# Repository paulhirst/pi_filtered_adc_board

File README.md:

# pi_filtered_adc_board
PCB for R-pi with 8-channel ADC with 2nd order active low pass filters.

This is a KiCad schematic and PCB design for a PCB that connects to a
Raspberry Pi via the 40-pin GPIO connector. The board hosts an 8-channel
ADC connected vi SPI to the R-Pi, with single supply op-amps and passive
component positions to implement a 2nd-order Butterworth low-pass filter
on each channel. 

A convenient pin-grid is supplies to connect the ADC to the SPI0 or SPI1 
interfaces on the R-Pi, or to connect the SPI interface of the ADC to any
R-Pi GPIO pins.

If you don't want to implement 2nd order filters on the inputs, you can simply
omit the filter capacitors and replace resistors with wire links to use the 
opamps and simple buffers, or you could place resistors to set gain.

Resistor placements are provided to allow for example forming a potential 
divider with an on-board resistor and an off-board thermistor. The on-board
resistor placements can be shorted to provide +3.3 or +5v (selectable) on the
inputs D connector, providing for either 2 or 3-pin inputs (ie resistor or
potentiometer style inputs).

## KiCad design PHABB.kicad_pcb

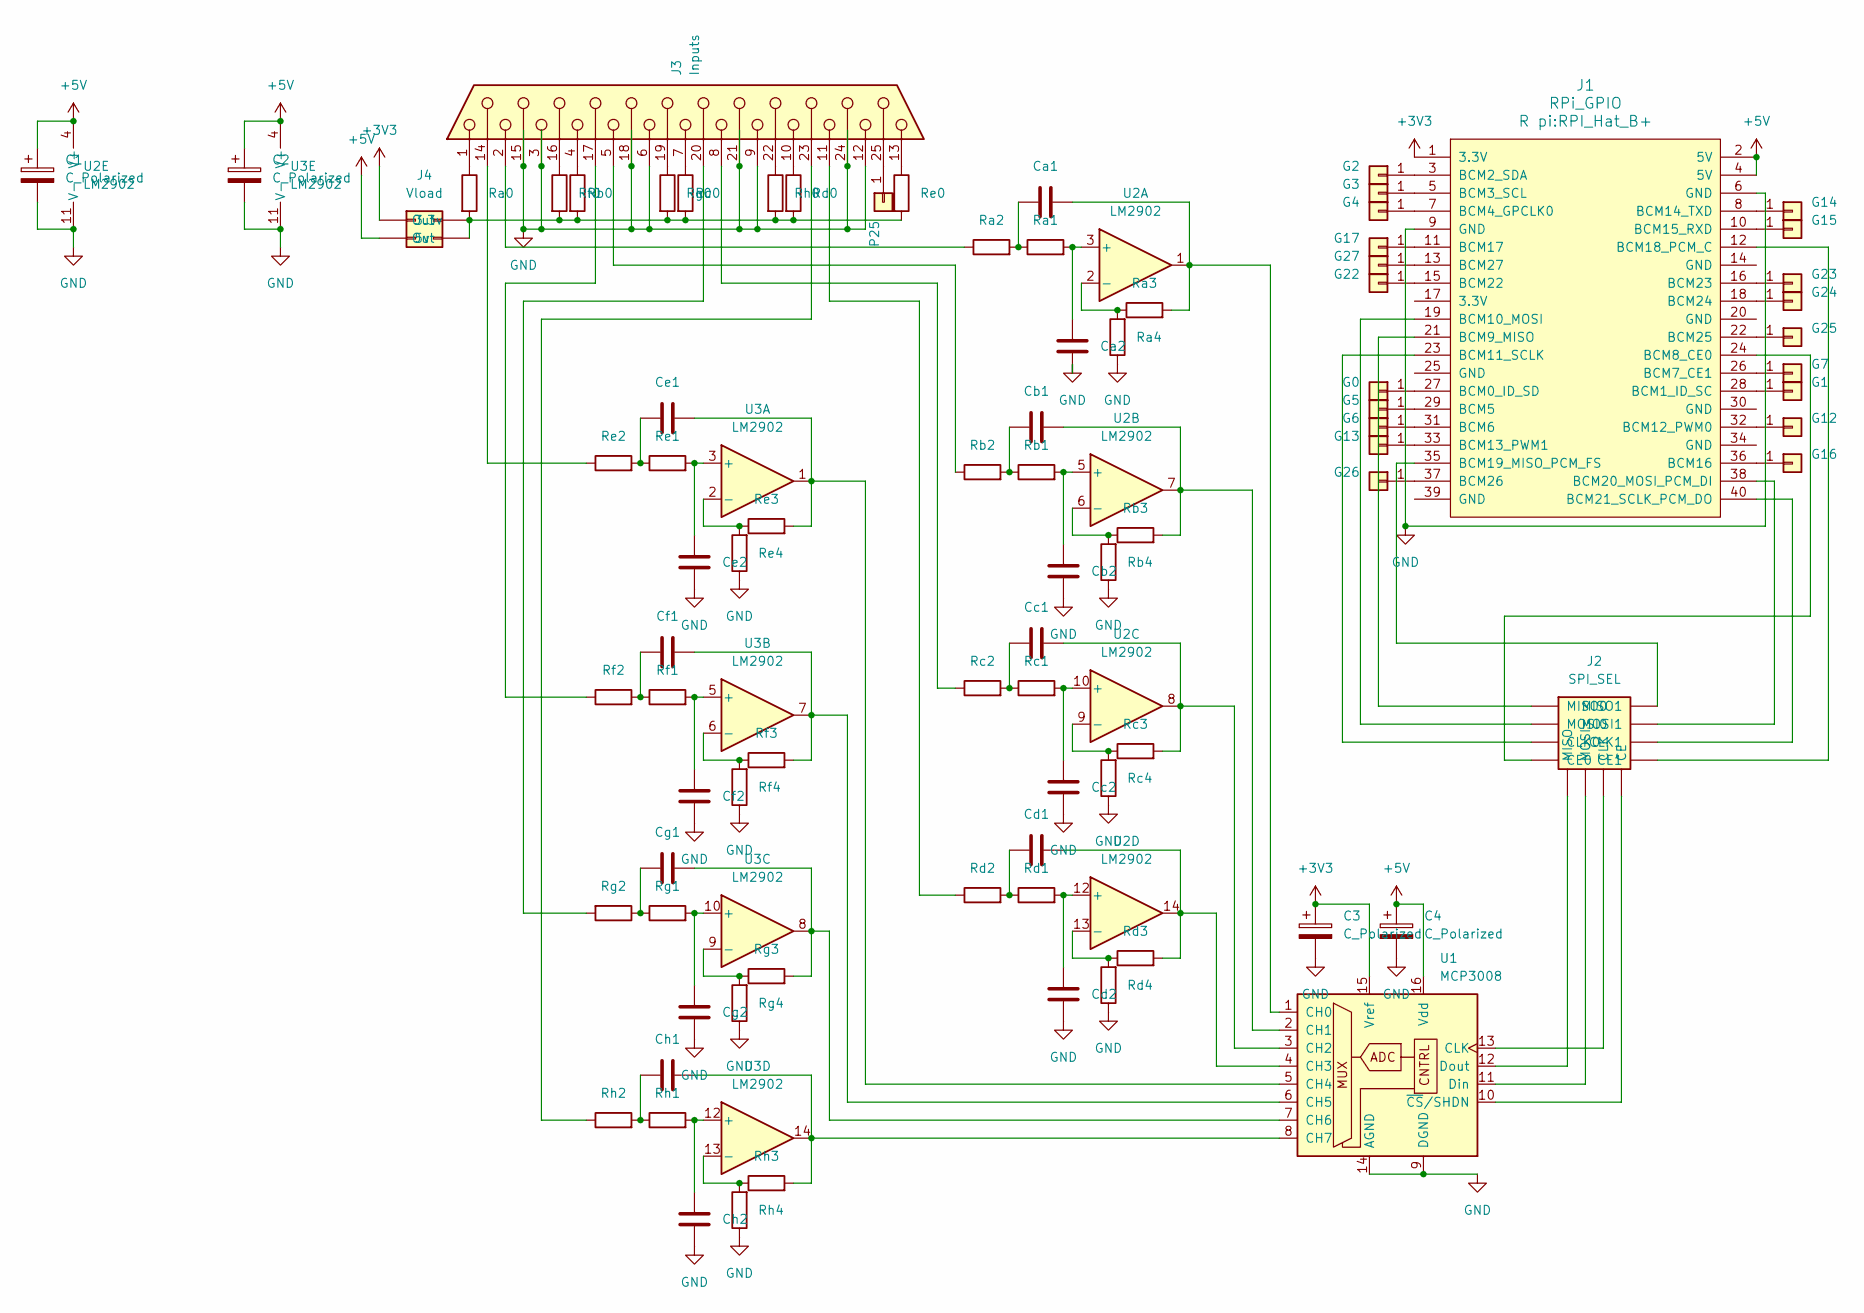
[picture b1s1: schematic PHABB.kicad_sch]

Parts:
C1, C2, C3, C4: C_Polarized; CP_Radial_D5.0mm_P2.50mm
Ca1, Ca2: C; C_Disc_D7.5mm_W5.0mm_P10.00mm
Cb1, Cb2: C; C_Disc_D7.5mm_W5.0mm_P10.00mm
Cc1, Cc2: C; C_Disc_D7.5mm_W5.0mm_P10.00mm
Cd1, Cd2: C; C_Disc_D7.5mm_W5.0mm_P10.00mm
Ce1, Ce2: C; C_Disc_D7.5mm_W5.0mm_P10.00mm
Cf1, Cf2: C; C_Disc_D7.5mm_W5.0mm_P10.00mm
Cg1, Cg2: C; C_Disc_D7.5mm_W5.0mm_P10.00mm
Ch1, Ch2: C; C_Disc_D7.5mm_W5.0mm_P10.00mm
G0: GPIO0; PinHeader_1x01_P2.54mm_Vertical
G1: GPIO1; PinHeader_1x01_P2.54mm_Vertical
G2: GPIO2; PinHeader_1x01_P2.54mm_Vertical
G3: GPIO3; PinHeader_1x01_P2.54mm_Vertical
G4: GPIO4; PinHeader_1x01_P2.54mm_Vertical
G5: GPIO5; PinHeader_1x01_P2.54mm_Vertical
G6: GPIO6; PinHeader_1x01_P2.54mm_Vertical
G7: GPIO07; PinHeader_1x01_P2.54mm_Vertical
G12: GPIO12; PinHeader_1x01_P2.54mm_Vertical
G13: GPIO13; PinHeader_1x01_P2.54mm_Vertical
G14: GPIO14; PinHeader_1x01_P2.54mm_Vertical
G15: GPIO15; PinHeader_1x01_P2.54mm_Vertical
G16: GPIO16; PinHeader_1x01_P2.54mm_Vertical
G17: GPIO17; PinHeader_1x01_P2.54mm_Vertical
G22: GPIO22; PinHeader_1x01_P2.54mm_Vertical
G23: GPIO23; PinHeader_1x01_P2.54mm_Vertical
G24: GPIO24; PinHeader_1x01_P2.54mm_Vertical
G25: GPIO25; PinHeader_1x01_P2.54mm_Vertical
G26: GPIO26; PinHeader_1x01_P2.54mm_Vertical
G27: GPIO27; PinHeader_1x01_P2.54mm_Vertical
J1: RPi_GPIO; RPI_Hat_B+
J2: SPI_SEL; 3x4 pingrid
J3: Inputs; DSUB-25_Female_Horizontal_P2.77x2.54mm_EdgePinOffset9.40mm
J4: Vload; PinHeader_2x02_P2.54mm_Vertical
P25: GPIO2; PinHeader_1x01_P2.54mm_Vertical
Ra0, Ra1, Ra2, Ra3, Ra4: R; R_Axial_DIN0204_L3.6mm_D1.6mm_P7.62mm_Horizontal
Rb0, Rb1, Rb2, Rb3, Rb4: R; R_Axial_DIN0204_L3.6mm_D1.6mm_P7.62mm_Horizontal
Rc0, Rc1, Rc2, Rc3, Rc4: R; R_Axial_DIN0204_L3.6mm_D1.6mm_P7.62mm_Horizontal
Rd0, Rd1, Rd2, Rd3, Rd4: R; R_Axial_DIN0204_L3.6mm_D1.6mm_P7.62mm_Horizontal
Re0, Re1, Re2, Re3, Re4: R; R_Axial_DIN0204_L3.6mm_D1.6mm_P7.62mm_Horizontal
Rf0, Rf1, Rf2, Rf3, Rf4: R; R_Axial_DIN0204_L3.6mm_D1.6mm_P7.62mm_Horizontal
Rg0, Rg1, Rg2, Rg3, Rg4: R; R_Axial_DIN0204_L3.6mm_D1.6mm_P7.62mm_Horizontal
Rh0, Rh1, Rh2, Rh3, Rh4: R; R_Axial_DIN0204_L3.6mm_D1.6mm_P7.62mm_Horizontal
U1: MCP3008; DIP-16_W7.62mm
U2, U3: LM2902; DIP-14_W7.62mm

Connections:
+3V3: C3.1, J1.1 (3.3V), J4.1 (3.3v), U1.15 (Vref)
+5V: C1.1, C2.1, C4.1, J1.2 (5V), J1.4 (5V), J4.3 (5v), U1.16 (Vdd), U2.4 (V+), U3.4 (V+)
GND: C1.2, C2.2, C3.2, C4.2, Ca2.2, Cb2.2, Cc2.2, Cd2.2, Ce2.2, Cf2.2, Cg2.2, Ch2.2, J1.6 (GND), J1.9 (GND), J3.3, J3.6, J3.9, J3.12, J3.15, J3.18, J3.21, J3.24, Ra4.1, Rb4.1, Rc4.1, Rd4.1, Re4.1, Rf4.1, Rg4.1, Rh4.1, U1.9 (DGND), U1.14 (AGND), U2.11 (V-), U3.11 (V-)
unnamed: Ca1.1, Ra1.1, Ra2.2
unnamed: Cb1.1, Rb1.1, Rb2.2
unnamed: Cc1.1, Rc1.1, Rc2.2
unnamed: Cd1.1, Rd1.1, Rd2.2
unnamed: Ce1.1, Re1.1, Re2.2
unnamed: Cf1.1, Rf1.1, Rf2.2
unnamed: Cg1.1, Rg1.1, Rg2.1
unnamed: Ch1.1, Rh1.1, Rh2.2
unnamed: G0.1, J1.27 (BCM0_ID_SD)
unnamed: G1.1, J1.28 (BCM1_ID_SC)
unnamed: G2.1, J1.3 (BCM2_SDA)
unnamed: G3.1, J1.5 (BCM3_SCL)
unnamed: G4.1, J1.7 (BCM4_GPCLK0)
unnamed: G5.1, J1.29 (BCM5)
unnamed: G6.1, J1.31 (BCM6)
unnamed: G7.1, J1.26 (BCM7_CE1)
unnamed: G12.1, J1.32 (BCM12_PWM0)
unnamed: G13.1, J1.33 (BCM13_PWM1)
unnamed: G14.1, J1.8 (BCM14_TXD)
unnamed: G15.1, J1.10 (BCM15_RXD)
unnamed: G16.1, J1.36 (BCM16)
unnamed: G17.1, J1.11 (BCM17)
unnamed: G22.1, J1.15 (BCM22)
unnamed: G23.1, J1.16 (BCM23)
unnamed: G24.1, J1.18 (BCM24)
unnamed: G25.1, J1.22 (BCM25)
unnamed: G26.1, J1.37 (BCM26)
unnamed: G27.1, J1.13 (BCM27)
unnamed: J1.24 (BCM8_CE0), J2.4 (CE0)
unnamed: J1.21 (BCM9_MISO), J2.1 (MISO0)
unnamed: J1.19 (BCM10_MOSI), J2.2 (MOSI0)
unnamed: J1.23 (BCM11_SCLK), J2.3 (CLK0)
unnamed: J1.12 (BCM18_PCM_C), J2.8 (CE1)
unnamed: J1.35 (BCM19_MISO_PCM_FS), J2.5 (MISO1)
unnamed: J1.38 (BCM20_MOSI_PCM_DI), J2.6 (MOSI1)
unnamed: J1.40 (BCM21_SCLK_PCM_DO), J2.7 (CLK1)
unnamed: J2.12 (CE), U1.10 (~CS/SHDN)
unnamed: J2.11 (CLK), U1.13 (CLK)
unnamed: J2.9 (MISO), U1.12 (Dout)
unnamed: J2.10 (MOSI), U1.11 (Din)
unnamed: J3.14, Re2.1
unnamed: J3.16, Rf0.1
unnamed: J3.17, Rf2.1
unnamed: J3.19, Rg0.1
unnamed: J3.20, Rg2.2
unnamed: J3.22, Rh0.1
unnamed: J3.23, Rh2.1
unnamed: J3.25, P25.1
unnamed: J3.1, Ra0.1
unnamed: J3.2, Ra2.1
unnamed: J3.4, Rb0.1
unnamed: J3.5, Rb2.1
unnamed: J3.7, Rc0.1
unnamed: J3.8, Rc2.1
unnamed: J3.10, Rd0.1
unnamed: J3.11, Rd2.1
unnamed: J3.13, Re0.1
unnamed: J4.2 (Out), J4.4 (Out), Ra0.2, Rb0.2, Rc0.2, Rd0.2, Re0.2, Rf0.2, Rg0.2, Rh0.2
unnamed: Ca1.2, Ra3.2, U1.1 (CH0), U2.1
unnamed: Cb1.2, Rb3.2, U1.2 (CH1), U2.7
unnamed: Cc1.2, Rc3.2, U1.3 (CH2), U2.8
unnamed: Cd1.2, Rd3.2, U1.4 (CH3), U2.14
unnamed: Ce1.2, Re3.2, U1.5 (CH4), U3.1
unnamed: Cf1.2, Rf3.2, U1.6 (CH5), U3.7
unnamed: Cg1.2, Rg3.2, U1.7 (CH6), U3.8
unnamed: Ch1.2, Rh3.2, U1.8 (CH7), U3.14
unnamed: Ca2.1, Ra1.2, U2.3 (+)
unnamed: Ra3.1, Ra4.2, U2.2 (-)
unnamed: Cb2.1, Rb1.2, U2.5 (+)
unnamed: Rb3.1, Rb4.2, U2.6 (-)
unnamed: Cc2.1, Rc1.2, U2.10 (+)
unnamed: Rc3.1, Rc4.2, U2.9 (-)
unnamed: Cd2.1, Rd1.2, U2.12 (+)
unnamed: Rd3.1, Rd4.2, U2.13 (-)
unnamed: Ce2.1, Re1.2, U3.3 (+)
unnamed: Re3.1, Re4.2, U3.2 (-)
unnamed: Cf2.1, Rf1.2, U3.5 (+)
unnamed: Rf3.1, Rf4.2, U3.6 (-)
unnamed: Cg2.1, Rg1.2, U3.10 (+)
unnamed: Rg3.1, Rg4.2, U3.9 (-)
unnamed: Ch2.1, Rh1.2, U3.12 (+)
unnamed: Rh3.1, Rh4.2, U3.13 (-)

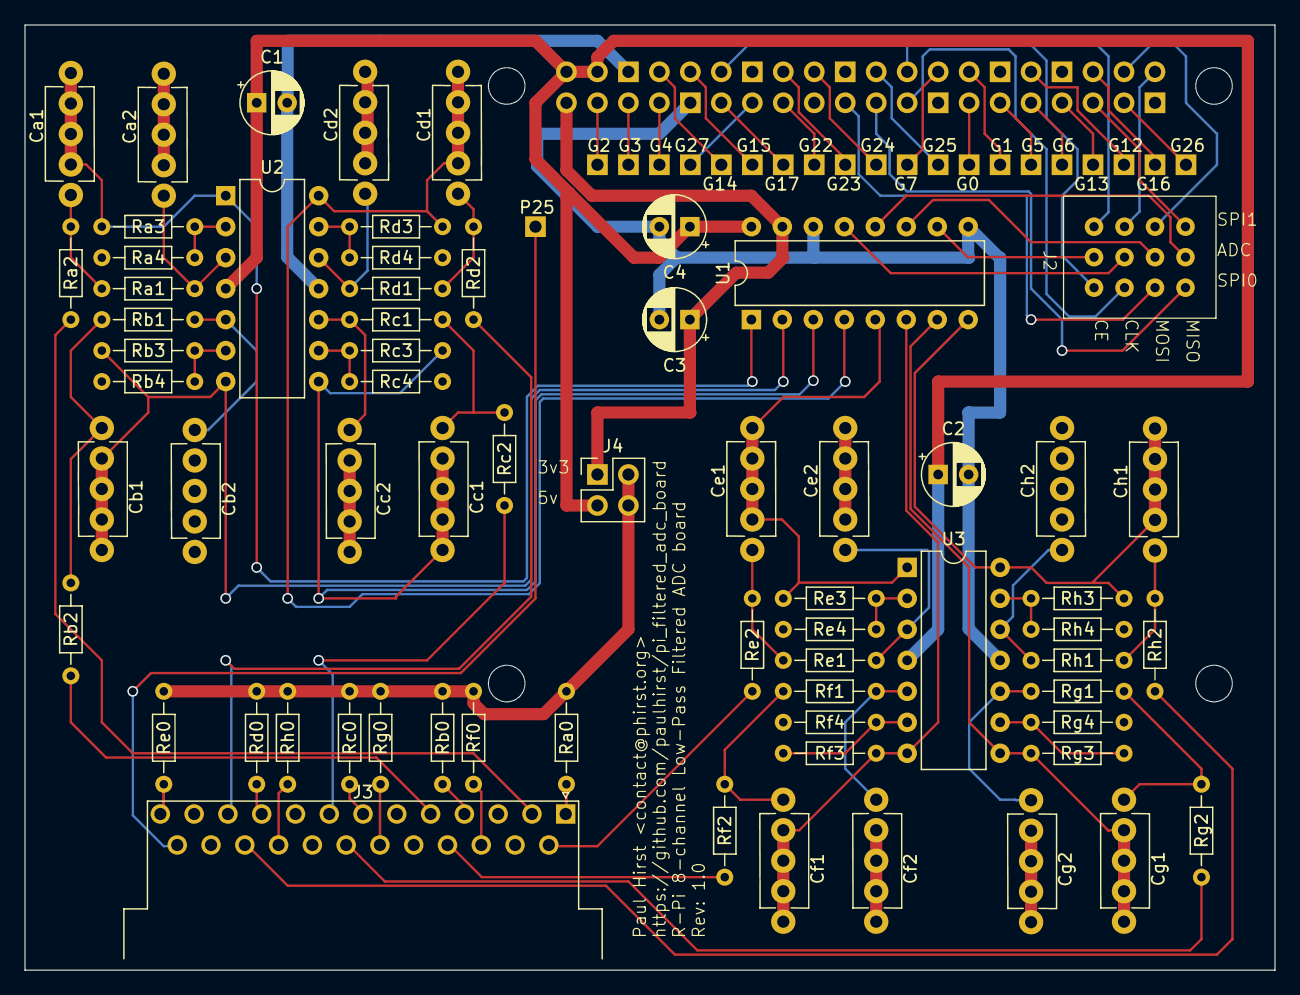
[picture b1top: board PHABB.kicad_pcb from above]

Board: 2 copper layers, 102.5 x 77.5 mm, 88 parts (0 on the bottom side), 85 nets.

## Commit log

2024-12-12 add ID text for rev 1.0
